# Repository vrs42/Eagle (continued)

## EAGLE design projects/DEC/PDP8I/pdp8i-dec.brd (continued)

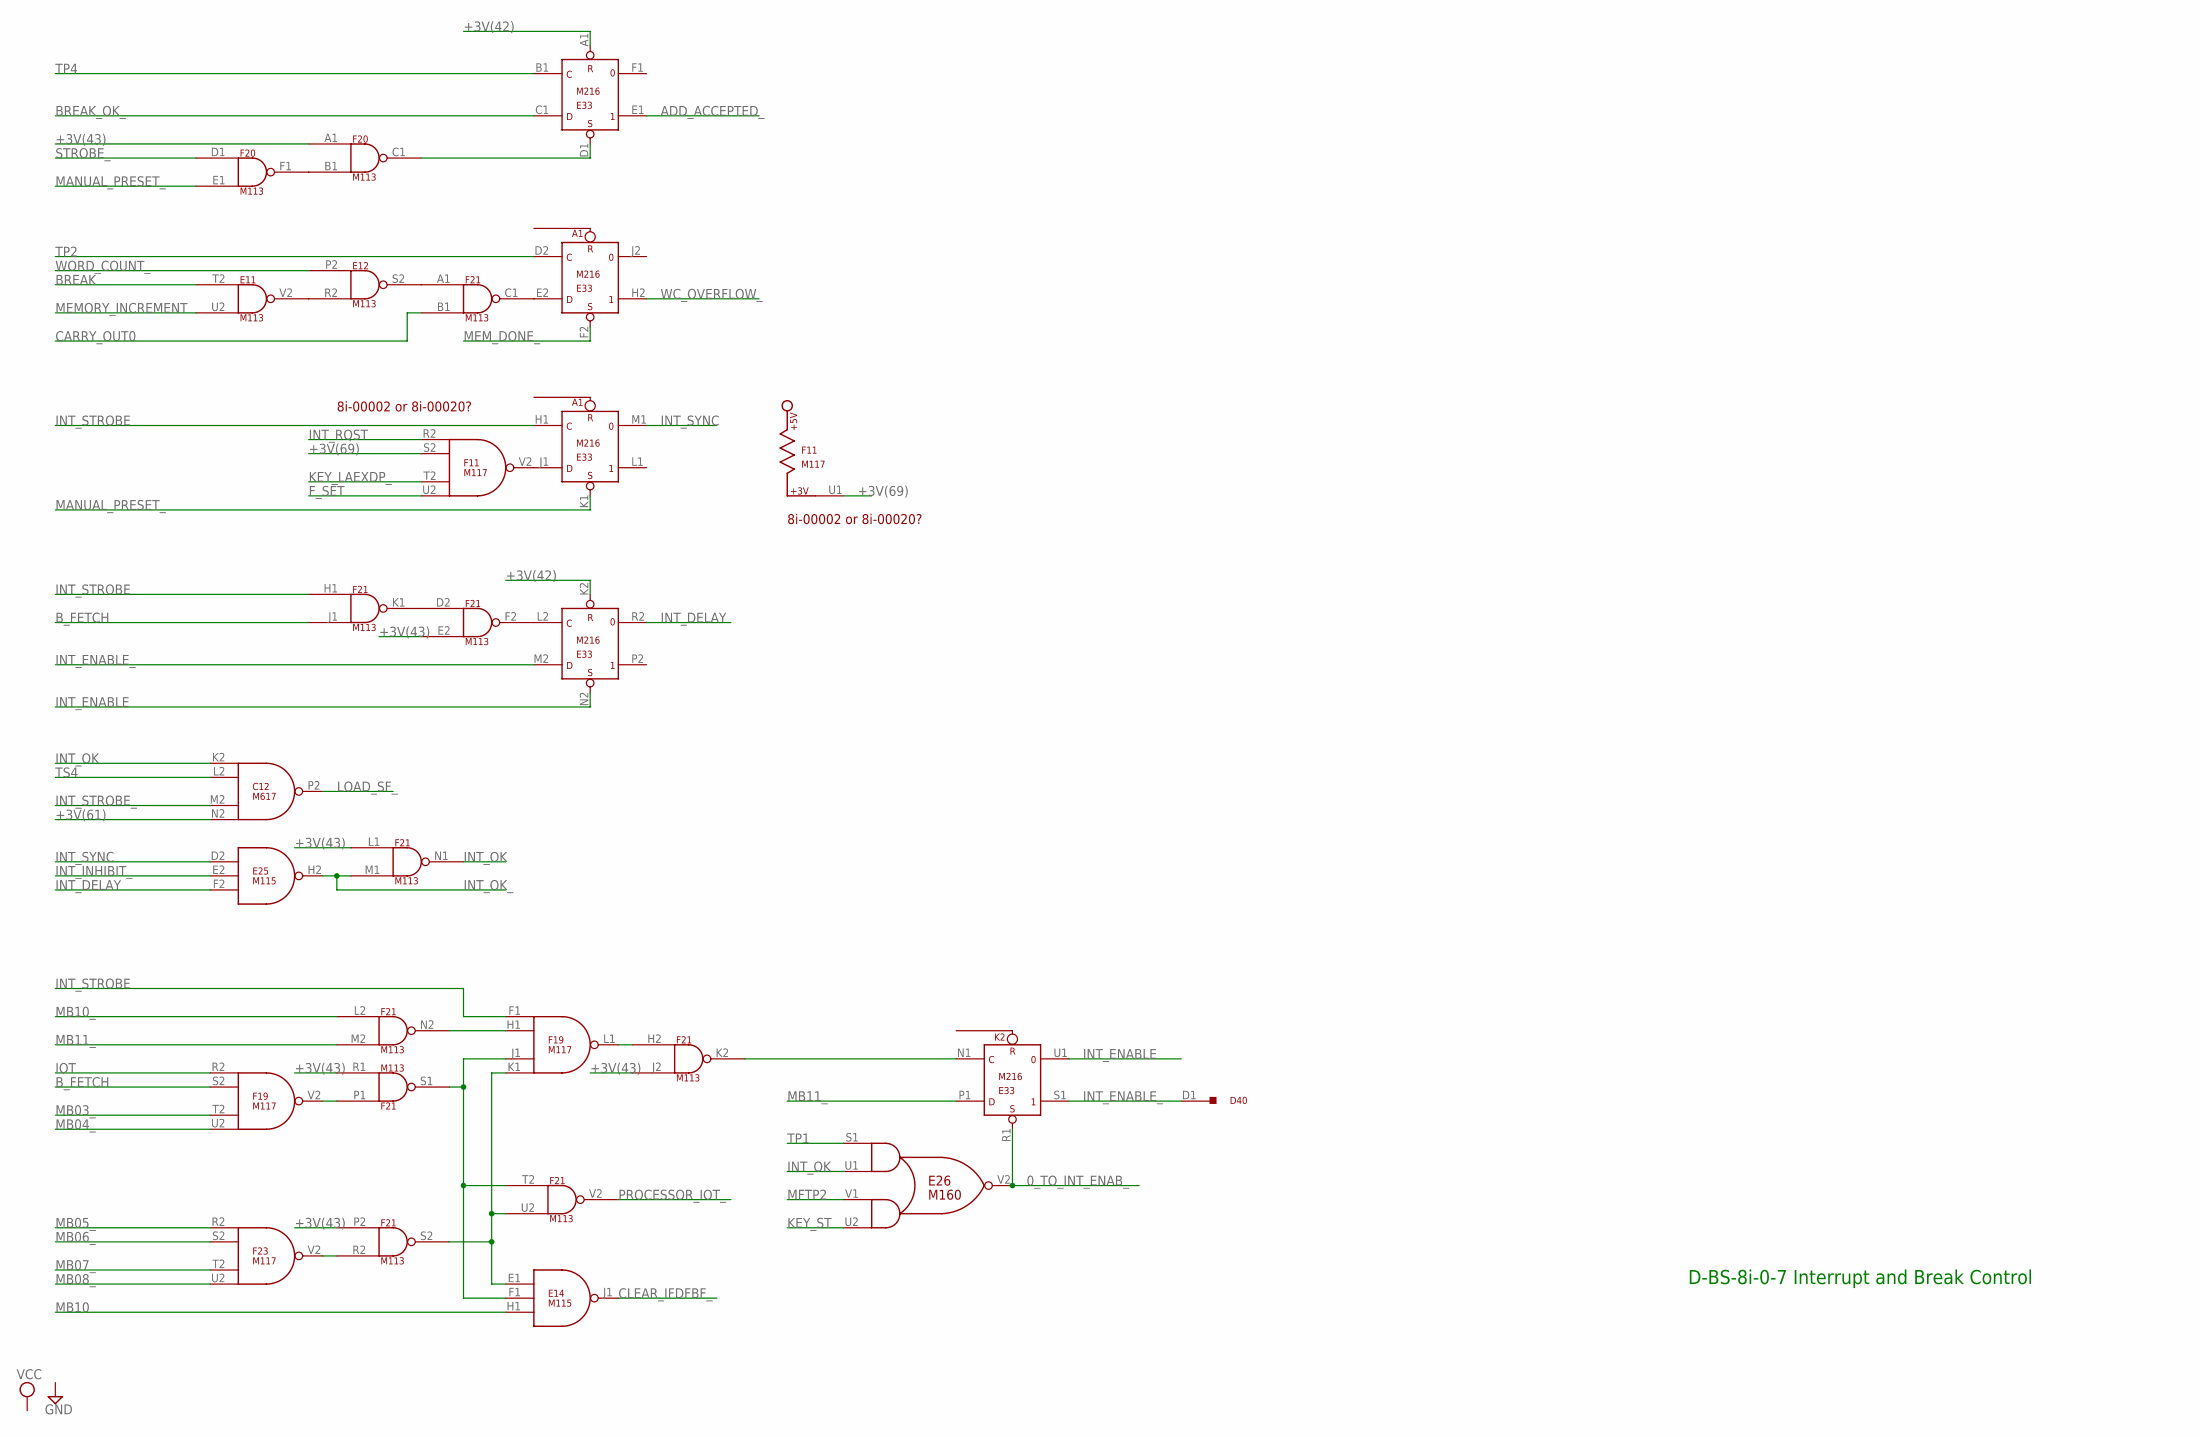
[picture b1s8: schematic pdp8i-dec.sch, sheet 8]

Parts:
C12: M617; H807
D40: M900; H807
E11, E12: M113; H807
E14, E25: M115; H807
E26: M160; H807
E33: M216; H807
F11, F19, F23: M117; H807
F20, F21: M113; H807

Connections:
0_TO_INT_ENAB_: E26.V2 (OUT), E33.R1 (S)
+3V(42): E33.A1 (R), E33.K2 (R); also elsewhere on the board
+3V(43): F20.A1 (IN1), F21.E2 (IN2), F21.J2 (IN2), F21.L1 (IN1), F21.P2 (IN1), F21.R1 (IN2); also elsewhere on the board
+3V(61): C12.N2 (IN4); also elsewhere on the board
+3V(69): F11.S2 (IN2), F11.U1; also elsewhere on the board
ADD_ACCEPTED_: E33.E1 (1); also elsewhere on the board
BREAK: E11.T2 (IN1); also elsewhere on the board
BREAK_OK_: E33.C1 (D); also elsewhere on the board
B_FETCH: F19.S2 (IN2), F21.J1 (IN2); also elsewhere on the board
CARRY_OUT0: F21.B1 (IN2); also elsewhere on the board
CLEAR_IFDFBF_: E14.J1 (OUT); also elsewhere on the board
F_SET: F11.U2 (IN4); also elsewhere on the board
GND: C12.C2 (GND), C12.T1 (GND), E11.C2 (GND), E11.T1 (GND), E12.C2 (GND), E12.T1 (GND), E14.C2 (GND), E14.T1 (GND), E25.C2 (GND), E25.T1 (GND), E26.C2 (GND), E26.T1 (GND), E33.C2 (GND), E33.T1 (GND), F11.C2 (GND), F11.T1 (GND), F19.C2 (GND), F19.T1 (GND), F20.C2 (GND), F20.T1 (GND), F21.C2 (GND), F21.T1 (GND), F23.C2 (GND), F23.T1 (GND); also elsewhere on the board
INT_DELAY: E25.F2 (IN3), E33.R2 (0)
INT_ENABLE: E33.N2 (S), E33.U1 (0)
INT_ENABLE_: D40.D1, E33.M2 (D), E33.S1 (1)
INT_INHIBIT_: E25.E2 (IN2); also elsewhere on the board
INT_OK: C12.K2 (IN1), E26.U1 (IN1B), F21.N1 (OUT); also elsewhere on the board
INT_OK_: E25.H2 (OUT), F21.M1 (IN2); also elsewhere on the board
INT_RQST: F11.R2 (IN1); also elsewhere on the board
INT_STROBE: E33.H1 (C), F19.F1 (IN1), F21.H1 (IN1); also elsewhere on the board
INT_STROBE_: C12.M2 (IN3); also elsewhere on the board
INT_SYNC: E25.D2 (IN1), E33.M1 (0)
IOT: F19.R2 (IN1); also elsewhere on the board
KEY_LAEXDP_: F11.T2 (IN3); also elsewhere on the board
KEY_ST: E26.U2 (IN2B); also elsewhere on the board
LOAD_SF_: C12.P2 (OUT); also elsewhere on the board
MANUAL_PRESET_: E33.K1 (S), F20.E1 (IN2); also elsewhere on the board
MB03_: F19.T2 (IN3); also elsewhere on the board
MB04_: F19.U2 (IN4); also elsewhere on the board
MB05_: F23.R2 (IN1); also elsewhere on the board
MB06_: F23.S2 (IN2); also elsewhere on the board
MB07_: F23.T2 (IN3); also elsewhere on the board
MB08_: F23.U2 (IN4); also elsewhere on the board
MB10: E14.H1 (IN3); also elsewhere on the board
MB10_: F21.L2 (IN1); also elsewhere on the board
MB11_: E33.P1 (D), F21.M2 (IN2); also elsewhere on the board
MEMORY_INCREMENT: E11.U2 (IN2); also elsewhere on the board
MEM_DONE_: E33.F2 (S); also elsewhere on the board
MFTP2: E26.V1 (IN2A); also elsewhere on the board
unnamed: E33.J1 (D), F11.V2 (OUT)
unnamed: F20.B1 (IN2), F20.F1 (OUT)
unnamed: E33.D1 (S), F20.C1 (OUT)
unnamed: E11.V2 (OUT), E12.R2 (IN2)
unnamed: E12.S2 (OUT), F21.A1 (IN1)
unnamed: E33.E2 (D), F21.C1 (OUT)
unnamed: F21.D2 (IN1), F21.K1 (OUT)
unnamed: E33.L2 (C), F21.F2 (OUT)
unnamed: E33.N1 (C), F21.K2 (OUT)
unnamed: F19.H1 (IN2), F21.N2 (OUT)
unnamed: E14.F1 (IN2), F19.J1 (IN3), F21.S1 (OUT), F21.T2 (IN1)
unnamed: F19.V2 (OUT), F21.P1 (IN1)
unnamed: F19.L1 (OUT), F21.H2 (IN1)
unnamed: F21.R2 (IN2), F23.V2 (OUT)
unnamed: E14.E1 (IN1), F19.K1 (IN4), F21.S2 (OUT), F21.U2 (IN2)
PROCESSOR_IOT_: F21.V2 (OUT); also elsewhere on the board
STROBE_: F20.D1 (IN1); also elsewhere on the board
TP1: E26.S1 (IN1A); also elsewhere on the board
TP2: E33.D2 (C); also elsewhere on the board
TP4: E33.B1 (C); also elsewhere on the board
TS4: C12.L2 (IN2); also elsewhere on the board
VCC: C12.A2 (VCC), E11.A2 (VCC), E12.A2 (VCC), E14.A2 (VCC), E25.A2 (VCC), E26.A2 (VCC), E33.A2 (VCC), F11.A2 (VCC), F19.A2 (VCC), F20.A2 (VCC), F21.A2 (VCC), F23.A2 (VCC); also elsewhere on the board
WC_OVERFLOW_: E33.H2 (1); also elsewhere on the board
WORD_COUNT_: E12.P2 (IN1); also elsewhere on the board

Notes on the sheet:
D-BS-8i-0-7 Interrupt and Break Control
8i-00002 or 8i-00020?

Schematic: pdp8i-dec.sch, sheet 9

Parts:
C40: M900; H807
E33: M216; H807
E40: M900; H807
EF34, EF35, EF36, EF37, EF38, EF39: M220; H807-2
F28: M115; H807
F32: M113; H807
F33: M160; H807
F40: M900; H807

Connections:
+3V(42): E33.U2 (S); also elsewhere on the board
+3V(48): F32.P2 (IN1), F32.R1 (IN2), F32.T2 (IN1), F33.C1 (IN1C), F33.D2 (IN1A), F33.P1 (IN5C); also elsewhere on the board
AC00: EF34.BA1, F33.N2 (IN4A); also elsewhere on the board
AC00_: E40.V2, EF34.BB1; also elsewhere on the board
AC01: EF34.AV1; also elsewhere on the board
AC01_: E40.T2, EF34.AV2; also elsewhere on the board
AC02: EF35.BA1; also elsewhere on the board
AC02_: E40.J1, EF35.BB1; also elsewhere on the board
AC03: EF35.AV1; also elsewhere on the board
AC03_: E40.H2, EF35.AV2; also elsewhere on the board
AC04: EF36.BA1; also elsewhere on the board
AC04_: E40.M1, EF36.BB1; also elsewhere on the board
AC05: EF36.AV1; also elsewhere on the board
AC05_: E40.B1, EF36.AV2; also elsewhere on the board
AC06: EF37.BA1; also elsewhere on the board
AC06_: EF37.BB1, F40.V2; also elsewhere on the board
AC07: EF37.AV1; also elsewhere on the board
AC07_: EF37.AV2, F40.T2; also elsewhere on the board
AC08: EF38.BA1; also elsewhere on the board
AC08_: EF38.BB1, F40.J1; also elsewhere on the board
AC09: EF38.AV1; also elsewhere on the board
AC09_: EF38.AV2, F40.H2; also elsewhere on the board
AC10: EF39.BA1; also elsewhere on the board
AC10_: EF39.BB1, F40.M1; also elsewhere on the board
AC11: EF39.AV1; also elsewhere on the board
AC11_: EF39.AV2, F40.B1; also elsewhere on the board
AC_LOAD: E33.S2 (C), EF34.AU1, EF35.AU1, EF36.AU1, EF37.AU1, EF38.AU1, EF39.AU1; also elsewhere on the board
ADDER00: F33.K1 (IN4A); also elsewhere on the board
ADDER01: F33.M1 (IN5A); also elsewhere on the board
ADDER10: F33.E1 (IN2A); also elsewhere on the board
ADDER11: F32.P1 (IN1); also elsewhere on the board
ADDER11_: F28.P1 (IN1), F32.S1 (OUT); also elsewhere on the board
ADDER_L_: F33.H1 (IN3A), F33.V2 (OUT); also elsewhere on the board
ASR_ENABLE: F33.R2 (IN4C); also elsewhere on the board
ASR_L_SET_: F33.B1 (IN1B); also elsewhere on the board
B_EAE_ON: F33.P2 (IN4B); also elsewhere on the board
CARRY_OUT0: F32.V2 (OUT), F33.U1 (IN1B); also elsewhere on the board
CARRY_OUT0_: F32.U2 (IN2), F33.U2 (IN2B); also elsewhere on the board
DOUBLE_LEFT_ROTATE: F33.N1 (IN5B); also elsewhere on the board
DOUBLE_RIGHT_ROTATE: F33.F1 (IN2B); also elsewhere on the board
EAE_IR2_: F33.S2 (IN4D); also elsewhere on the board
EAE_ON_: F28.R1 (IN2); also elsewhere on the board
GND: C40.C2, E33.C2 (GND), E33.T1 (GND), E40.C2, EF34.AC2 (GND), EF34.AT1 (GND), EF34.BC2 (GND), EF34.BT1 (GND), EF35.AC2 (GND), EF35.AT1 (GND), EF35.BC2 (GND), EF35.BT1 (GND), EF36.AC2 (GND), EF36.AT1 (GND), EF36.BC2 (GND), EF36.BT1 (GND), EF37.AC2 (GND), EF37.AT1 (GND), EF37.BC2 (GND), EF37.BT1 (GND), EF38.AC2 (GND), EF38.AT1 (GND), EF38.BC2 (GND), EF38.BT1 (GND), EF39.AC2 (GND), EF39.AT1 (GND), EF39.BC2 (GND), EF39.BT1 (GND), F28.C2 (GND), F28.T1 (GND), F32.C2 (GND), F32.T1 (GND), F33.C2 (GND), F33.T1 (GND), F40.C2; also elsewhere on the board
LBAR_ENABLE: F33.M2 (IN3B); also elsewhere on the board
LEFT_SHIFT: F33.L1 (IN4B); also elsewhere on the board
LINK: E33.V2 (1), F33.J2 (IN2A); also elsewhere on the board
LINK_: C40.B1, E33.V1 (0), F33.L2 (IN3A)
L_ENABLE: F33.K2 (IN2B); also elsewhere on the board
MA00: EF34.AM2; also elsewhere on the board
MA00_: E40.U2, EF34.AM1; also elsewhere on the board
MA01: EF34.AL2; also elsewhere on the board
MA01_: E40.R2, EF34.AL1; also elsewhere on the board
MA02: EF35.AM2; also elsewhere on the board
MA02_: E40.K2, EF35.AM1; also elsewhere on the board
MA03: EF35.AL2; also elsewhere on the board
MA03_: E40.E2, EF35.AL1; also elsewhere on the board
MA04: EF36.AM2; also elsewhere on the board
MA04_: E40.L1, EF36.AM1; also elsewhere on the board
MA05: EF36.AL2; also elsewhere on the board
MA05_: E40.E1, EF36.AL1; also elsewhere on the board
MA06: EF37.AM2; also elsewhere on the board
MA06_: EF37.AM1, F40.U2; also elsewhere on the board
MA07: EF37.AL2; also elsewhere on the board
MA07_: EF37.AL1, F40.R2; also elsewhere on the board
MA08: EF38.AM2; also elsewhere on the board
MA08_: EF38.AM1, F40.K2; also elsewhere on the board
MA09: EF38.AL2; also elsewhere on the board
MA09_: EF38.AL1, F40.E2; also elsewhere on the board
MA10: EF39.AM2; also elsewhere on the board
MA10_: EF39.AM1, F40.L1; also elsewhere on the board
MA11: EF39.AL2; also elsewhere on the board
MA11_: EF39.AL1, F40.E1; also elsewhere on the board
MA_LOAD: EF34.AK1, EF35.AK1, EF36.AK1, EF37.AK1, EF38.AK1, EF39.AK1; also elsewhere on the board
MB00: EF34.AT2; also elsewhere on the board
MB00_: E40.R1, EF34.AU2; also elsewhere on the board
MB01: EF34.AS2; also elsewhere on the board
MB01_: E40.P1, EF34.AS1; also elsewhere on the board
MB02: EF35.AT2; also elsewhere on the board
MB02_: E40.F2, EF35.AU2; also elsewhere on the board
MB03: EF35.AS2; also elsewhere on the board
MB03_: E40.D2, EF35.AS1; also elsewhere on the board
MB04: EF36.AT2; also elsewhere on the board
MB04_: E40.K1, EF36.AU2; also elsewhere on the board
MB05: EF36.AS2; also elsewhere on the board
MB05_: E40.A1, EF36.AS1; also elsewhere on the board
MB06: EF37.AT2; also elsewhere on the board
MB06_: EF37.AU2, F40.R1; also elsewhere on the board
MB07: EF37.AS2; also elsewhere on the board
MB07_: EF37.AS1, F40.P1; also elsewhere on the board
MB08: EF38.AT2; also elsewhere on the board
MB08_: EF38.AU2, F40.F2; also elsewhere on the board
MB09: EF38.AS2; also elsewhere on the board
MB09_: EF38.AS1, F40.D2; also elsewhere on the board
MB10: EF39.AT2; also elsewhere on the board
MB10_: EF39.AU2, F40.K1; also elsewhere on the board
MB11: EF39.AS2; also elsewhere on the board
MB11_: EF39.AS1, F40.A1; also elsewhere on the board
MB_LOAD: EF34.AR1, EF35.AR1, EF36.AR1, EF37.AR1, EF38.AR1, EF39.AR1; also elsewhere on the board
unnamed: E33.T2 (D), F33.R1 (OUT)
unnamed: F32.S2 (OUT), F33.V1 (IN2A)
unnamed: F28.U1 (OUT), F33.A1 (IN1A)
unnamed: F32.R2 (IN2), F33.S1 (IN1A), F33.T2 (OUT)
NO_SHIFT: F33.J1 (IN3B); also elsewhere on the board
PC00_: E40.J2, EF34.AR2
PC01_: E40.S1, EF34.AP2
PC02_: E40.P2, EF35.AR2
PC03_: E40.N1, EF35.AP2
PC04_: E40.C1, EF36.AR2
PC05_: E40.D1, EF36.AP2
PC06_: EF37.AR2, F40.J2
PC07_: EF37.AP2, F40.S1
PC08_: EF38.AR2, F40.P2
PC09_: EF38.AP2, F40.N1
PC10_: EF39.AR2, F40.C1
PC11_: EF39.AP2, F40.D1
PC_LOAD: EF34.AN2, EF35.AN2, EF36.AN2, EF37.AN2, EF38.AN2, EF39.AN2; also elsewhere on the board
RIGHT_SHIFT: F33.D1 (IN1D); also elsewhere on the board
TT_DATA: F33.H2 (IN1D); also elsewhere on the board
TT_INST_: F28.S1 (IN3), F33.F2 (IN1C); also elsewhere on the board
TT_SHIFT_ENABLE: F33.E2 (IN1B); also elsewhere on the board
VCC: C40.A2, E33.A2 (VCC), E40.A2, EF34.AA2 (VCC), EF34.BA2 (VCC), EF35.AA2 (VCC), EF35.BA2 (VCC), EF36.AA2 (VCC), EF36.BA2 (VCC), EF37.AA2 (VCC), EF37.BA2 (VCC), EF38.AA2 (VCC), EF38.BA2 (VCC), EF39.AA2 (VCC), EF39.BA2 (VCC), F28.A2 (VCC), F32.A2 (VCC), F33.A2 (VCC), F40.A2; also elsewhere on the board

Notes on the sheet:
D-BS-8i-0-8 Major Registers
REG_BUS00
REG_BUS01
REG_BUS02
REG_BUS03
REG_BUS04
REG_BUS05
REG_BUS06
REG_BUS07
REG_BUS08
REG_BUS09
REG_BUS10
REG_BUS11

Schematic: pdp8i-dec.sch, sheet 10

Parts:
A40: W077; H807
EF34, EF35: M220; H807-2

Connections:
ACBAR_ENABLE: EF34.BJ2, EF35.BJ2; also elsewhere on the board
AC_ENABLE: EF34.BH2, EF35.BH2; also elsewhere on the board
ADDER00: EF34.AE2, EF35.AB1; also elsewhere on the board
ADDER01: EF34.AF1, EF35.AC1; also elsewhere on the board
ADDER02: EF34.AH2, EF35.AE2, EF35.BB2; also elsewhere on the board
ADDER03: EF34.AJ2, EF35.AF1; also elsewhere on the board
ADDER04: EF35.AH2; also elsewhere on the board
ADDER05: EF35.AJ2; also elsewhere on the board
ADDER11: EF34.AB1; also elsewhere on the board
ADDER_L_: EF34.AC1, EF34.BB2; also elsewhere on the board
AND_ENABLE: EF34.AA1, EF35.AA1; also elsewhere on the board
CARRY_OUT0_: EF34.BK2; also elsewhere on the board
DATA00: EF34.BM2; also elsewhere on the board
DATA01: EF34.BP2; also elsewhere on the board
DATA02: EF35.BM2; also elsewhere on the board
DATA_ADD00: EF34.BS1; also elsewhere on the board
DATA_ADD01: EF34.BU1; also elsewhere on the board
DATA_ADD02: EF35.BS1; also elsewhere on the board
DATA_ADD_ENABLE: EF34.BT2, EF35.BT2; also elsewhere on the board
DATA_ENABLE: EF34.BL1, EF35.BL1; also elsewhere on the board
DOUBLE_LEFT_ROTATE: EF34.AH1, EF35.AH1; also elsewhere on the board
DOUBLE_RIGHT_ROTATE: EF34.AD1, EF35.AD1; also elsewhere on the board
GND: EF34.AC2 (GND), EF34.AT1 (GND), EF34.BC2 (GND), EF34.BD1, EF34.BE2, EF34.BN1, EF34.BT1 (GND), EF35.AC2 (GND), EF35.AT1 (GND), EF35.BC2 (GND), EF35.BD1, EF35.BT1 (GND); also elsewhere on the board
INPUT_BUS00: EF34.BK1; also elsewhere on the board
INPUT_BUS01: EF34.BM1; also elsewhere on the board
INPUT_BUS02: EF35.BK1; also elsewhere on the board
IO_ENABLE: EF34.BL2, EF35.BL2; also elsewhere on the board
LEFT_SHIFT: EF34.AF2, EF35.AF2; also elsewhere on the board
MA_ENABLE0_4: EF34.BP1, EF34.BR2, EF35.BP1; also elsewhere on the board
MEM00: EF34.BR1; also elsewhere on the board
MEM01: EF34.BV2; also elsewhere on the board
MEM02: EF35.BR1; also elsewhere on the board
MEM_ENABLE0_4: EF34.BU2, EF34.BV1, EF35.BU2; also elsewhere on the board
MQ00: EF34.BH1; also elsewhere on the board
MQ01: EF34.BN2; also elsewhere on the board
MQ02: EF35.BH1; also elsewhere on the board
MQ_ENABLE: EF34.BF1, EF35.BF1; also elsewhere on the board
unnamed: EF34.BJ1, EF35.BK2
NO_SHIFT: EF34.AE1, EF35.AE1; also elsewhere on the board
PC_ENABLE: EF34.BS2, EF35.BS2; also elsewhere on the board
RIGHT_SHIFT: EF34.AD2, EF35.AD2; also elsewhere on the board
SC_ENABLE: EF34.BF2, EF35.BF2; also elsewhere on the board
SR00: A40.L2, EF34.BE1
SR01: A40.M2, EF34.BD2
SR02: A40.R2, EF35.BE1
SR_ENABLE: EF34.BC1, EF35.BC1; also elsewhere on the board
TT_LINE_SHIFT_: EF34.AB2, EF35.AB2; also elsewhere on the board
VCC: EF34.AA2 (VCC), EF34.BA2 (VCC), EF35.AA2 (VCC), EF35.BA2 (VCC); also elsewhere on the board

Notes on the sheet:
D-BS-8i-0-9 Major Registers Gating (1/4)
REG_BUS00
REG_BUS01
REG_BUS02
CARRY_OUT3_

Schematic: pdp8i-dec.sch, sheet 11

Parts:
A40: W077; H807
EF35, EF36: M220; H807-2

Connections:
ACBAR_ENABLE: EF36.BJ2; also elsewhere on the board
AC_ENABLE: EF36.BH2; also elsewhere on the board
ADDER02: EF36.AB1; also elsewhere on the board
ADDER03: EF36.AC1; also elsewhere on the board
ADDER04: EF36.AE2, EF36.BB2; also elsewhere on the board
ADDER05: EF36.AF1; also elsewhere on the board
ADDER06: EF36.AH2; also elsewhere on the board
ADDER07: EF36.AJ2; also elsewhere on the board
AND_ENABLE: EF36.AA1; also elsewhere on the board
CARRY_OUT6_: EF36.BJ1; also elsewhere on the board
DATA03: EF35.BP2; also elsewhere on the board
DATA04: EF36.BM2; also elsewhere on the board
DATA05: EF36.BP2; also elsewhere on the board
DATA_ADD03: EF35.BU1; also elsewhere on the board
DATA_ADD04: EF36.BS1; also elsewhere on the board
DATA_ADD05: EF36.BU1; also elsewhere on the board
DATA_ADD_ENABLE: EF36.BT2; also elsewhere on the board
DATA_ENABLE: EF36.BL1; also elsewhere on the board
DOUBLE_LEFT_ROTATE: EF36.AH1; also elsewhere on the board
DOUBLE_RIGHT_ROTATE: EF36.AD1; also elsewhere on the board
GND: EF35.AC2 (GND), EF35.AT1 (GND), EF35.BC2 (GND), EF35.BE2, EF35.BN1, EF35.BT1 (GND), EF36.AC2 (GND), EF36.AT1 (GND), EF36.BC2 (GND), EF36.BD1, EF36.BE2, EF36.BN1, EF36.BT1 (GND); also elsewhere on the board
INPUT_BUS03: EF35.BM1; also elsewhere on the board
INPUT_BUS04: EF36.BK1; also elsewhere on the board
INPUT_BUS05: EF36.BM1; also elsewhere on the board
IO_ENABLE: EF36.BL2; also elsewhere on the board
LEFT_SHIFT: EF36.AF2; also elsewhere on the board
MA_ENABLE0_4: EF35.BR2, EF36.BP1; also elsewhere on the board
MA_ENABLE5_11: EF36.BR2; also elsewhere on the board
MEM03: EF35.BV2; also elsewhere on the board
MEM04: EF36.BR1; also elsewhere on the board
MEM05: EF36.BV2; also elsewhere on the board
MEM_ENABLE0_4: EF35.BV1, EF36.BU2; also elsewhere on the board
MEM_ENABLE5_8: EF36.BV1; also elsewhere on the board
MQ03: EF35.BN2; also elsewhere on the board
MQ04: EF36.BH1; also elsewhere on the board
MQ05: EF36.BN2; also elsewhere on the board
MQ_ENABLE: EF36.BF1; also elsewhere on the board
unnamed: EF35.BJ1, EF36.BK2
NO_SHIFT: EF36.AE1; also elsewhere on the board
PC_ENABLE: EF36.BS2; also elsewhere on the board
RIGHT_SHIFT: EF36.AD2; also elsewhere on the board
SC_ENABLE: EF36.BF2; also elsewhere on the board
SR03: A40.S2, EF35.BD2
SR04: A40.T2, EF36.BE1
SR05: A40.U2, EF36.BD2
SR_ENABLE: EF36.BC1; also elsewhere on the board
TT_LINE_SHIFT_: EF36.AB2; also elsewhere on the board
VCC: EF35.AA2 (VCC), EF35.BA2 (VCC), EF36.AA2 (VCC), EF36.BA2 (VCC); also elsewhere on the board

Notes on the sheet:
D-BS-8i-0-9 Major Registers Gating (2/4)
REG_BUS03
REG_BUS04
REG_BUS05

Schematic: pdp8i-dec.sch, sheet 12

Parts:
A40: W077; H807
B40: W077; H807
EF37, EF38: M220; H807-2

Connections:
ACBAR_ENABLE: EF37.BJ2, EF38.BJ2; also elsewhere on the board
AC_ENABLE: EF37.BH2, EF38.BH2; also elsewhere on the board
ADDER04: EF37.AB1; also elsewhere on the board
ADDER05: EF37.AC1; also elsewhere on the board
ADDER06: EF37.AE2, EF37.BB2, EF38.AB1; also elsewhere on the board
ADDER07: EF37.AF1, EF38.AC1; also elsewhere on the board
ADDER08: EF37.AH2, EF38.AE2, EF38.BB2; also elsewhere on the board
ADDER09: EF37.AJ2, EF38.AF1; also elsewhere on the board
ADDER10: EF38.AH2; also elsewhere on the board
ADDER11: EF38.AJ2; also elsewhere on the board
AND_ENABLE: EF37.AA1, EF38.AA1; also elsewhere on the board
CARRY_OUT6_: EF37.BK2; also elsewhere on the board
DATA06: EF37.BM2; also elsewhere on the board
DATA07: EF37.BP2; also elsewhere on the board
DATA08: EF38.BM2; also elsewhere on the board
DATA_ADD06: EF37.BS1; also elsewhere on the board
DATA_ADD07: EF37.BU1; also elsewhere on the board
DATA_ADD08: EF38.BS1; also elsewhere on the board
DATA_ADD_ENABLE: EF37.BT2, EF38.BT2; also elsewhere on the board
DATA_ENABLE: EF37.BL1, EF38.BL1; also elsewhere on the board
DOUBLE_LEFT_ROTATE: EF37.AH1, EF38.AH1; also elsewhere on the board
DOUBLE_RIGHT_ROTATE: EF37.AD1, EF38.AD1; also elsewhere on the board
GND: A40.C2, B40.C2, EF37.AC2 (GND), EF37.AT1 (GND), EF37.BC2 (GND), EF37.BD1, EF37.BE2, EF37.BT1 (GND), EF38.AC2 (GND), EF38.AT1 (GND), EF38.BC2 (GND), EF38.BT1 (GND); also elsewhere on the board
INPUT_BUS06: EF37.BK1; also elsewhere on the board
INPUT_BUS07: EF37.BM1; also elsewhere on the board
INPUT_BUS08: EF38.BK1; also elsewhere on the board
IO_ENABLE: EF37.BL2, EF38.BL2; also elsewhere on the board
LEFT_SHIFT: EF37.AF2, EF38.AF2; also elsewhere on the board
MA_ENABLE5_11: EF37.BP1, EF37.BR2, EF38.BP1; also elsewhere on the board
MEM06: EF37.BR1; also elsewhere on the board
MEM07: EF37.BV2; also elsewhere on the board
MEM08: EF38.BR1; also elsewhere on the board
MEM_ENABLE5_8: EF37.BU2, EF37.BV1, EF38.BU2; also elsewhere on the board
MQ06: EF37.BH1; also elsewhere on the board
MQ07: EF37.BN2; also elsewhere on the board
MQ08: EF38.BH1; also elsewhere on the board
MQ_ENABLE: EF37.BF1, EF38.BF1; also elsewhere on the board
unnamed: EF37.BJ1, EF38.BK2
NO_SHIFT: EF37.AE1, EF38.AE1; also elsewhere on the board
PC_ENABLE: EF37.BS2, EF38.BS2; also elsewhere on the board
RIGHT_SHIFT: EF37.AD2, EF38.AD2; also elsewhere on the board
SC0: EF37.BN1; also elsewhere on the board
SC1: EF38.BD1; also elsewhere on the board
SC_ENABLE: EF37.BF2, EF38.BF2; also elsewhere on the board
SR06: A40.V2, EF37.BE1
SR07: B40.D2, EF37.BD2
SR08: B40.E2, EF38.BE1
SR_ENABLE: EF37.BC1, EF38.BC1; also elsewhere on the board
TT_LINE_SHIFT_: EF37.AB2, EF38.AB2; also elsewhere on the board
VCC: A40.A2, B40.A2, EF37.AA2 (VCC), EF37.BA2 (VCC), EF38.AA2 (VCC), EF38.BA2 (VCC); also elsewhere on the board

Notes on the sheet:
D-BS-8i-0-9 Major Registers Gating (3/4)
REG_BUS06
REG_BUS07
REG_BUS08
CARRY_OUT9_

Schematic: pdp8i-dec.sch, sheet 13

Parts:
B40: W077; H807
E24: M113; H807
E25: M115; H807
EF38, EF39: M220; H807-2

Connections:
ACBAR_ENABLE: EF39.BJ2; also elsewhere on the board
AC_ENABLE: EF39.BH2; also elsewhere on the board
ADDER00: EF39.AJ2; also elsewhere on the board
ADDER08: EF39.AB1; also elsewhere on the board
ADDER09: EF39.AC1; also elsewhere on the board
ADDER10: EF39.AE2, EF39.BB2; also elsewhere on the board
ADDER11: EF39.AF1; also elsewhere on the board
ADDER_L_: E24.B1 (IN2); also elsewhere on the board
AND_ENABLE: EF39.AA1; also elsewhere on the board
CARRY_INSERT_: EF39.BJ1; also elsewhere on the board
DATA09: EF38.BP2; also elsewhere on the board
DATA10: EF39.BM2; also elsewhere on the board
DATA11: EF39.BP2; also elsewhere on the board
DATA_ADD09: EF38.BU1; also elsewhere on the board
DATA_ADD10: EF39.BS1; also elsewhere on the board
DATA_ADD11: EF39.BU1; also elsewhere on the board
DATA_ADD_ENABLE: EF39.BT2; also elsewhere on the board
DATA_ENABLE: EF39.BL1; also elsewhere on the board
DOUBLE_LEFT_ROTATE: EF39.AH1; also elsewhere on the board
DOUBLE_RIGHT_ROTATE: EF39.AD1; also elsewhere on the board
E25D1: E25.D1 (OUT), EF39.AH2
EAE_MQ0BAR_ENABLE_: E25.B1 (IN2); also elsewhere on the board
EAE_MQ0_ENABLE_: E25.C1 (IN3); also elsewhere on the board
EAE_ON_: E24.A1 (IN1); also elsewhere on the board
GND: E24.C2 (GND), E24.T1 (GND), E25.C2 (GND), E25.T1 (GND), EF38.AC2 (GND), EF38.AT1 (GND), EF38.BC2 (GND), EF38.BE2, EF38.BT1 (GND), EF39.AC2 (GND), EF39.AT1 (GND), EF39.BC2 (GND), EF39.BT1 (GND); also elsewhere on the board
INPUT_BUS09: EF38.BM1; also elsewhere on the board
INPUT_BUS10: EF39.BK1; also elsewhere on the board
INPUT_BUS11: EF39.BM1; also elsewhere on the board
IO_ENABLE: EF39.BL2; also elsewhere on the board
LEFT_SHIFT: EF39.AF2; also elsewhere on the board
MA_ENABLE5_11: EF38.BR2, EF39.BP1, EF39.BR2; also elsewhere on the board
MEM09: EF38.BV2; also elsewhere on the board
MEM10: EF39.BR1; also elsewhere on the board
MEM11: EF39.BV2; also elsewhere on the board
MEM_ENABLE9_11: EF38.BV1, EF39.BU2, EF39.BV1; also elsewhere on the board
MQ09: EF38.BN2; also elsewhere on the board
MQ10: EF39.BH1; also elsewhere on the board
MQ11: EF39.BN2; also elsewhere on the board
MQ_ENABLE: EF39.BF1; also elsewhere on the board
unnamed: EF38.BJ1, EF39.BK2
unnamed: E24.C1 (OUT), E25.A1 (IN1)
NO_SHIFT: EF39.AE1; also elsewhere on the board
PC_ENABLE: EF39.BS2; also elsewhere on the board
RIGHT_SHIFT: EF39.AD2; also elsewhere on the board
SC2: EF38.BN1; also elsewhere on the board
SC3: EF39.BD1; also elsewhere on the board
SC4: EF39.BN1; also elsewhere on the board
SC_ENABLE: EF39.BF2; also elsewhere on the board
SR09: B40.F2, EF38.BD2
SR10: B40.H2, EF39.BE1
SR11: B40.J2, EF39.BD2
SR_ENABLE: EF39.BC1; also elsewhere on the board
TT_CARRY_INSERT_S: EF39.BE2; also elsewhere on the board
TT_LINE_SHIFT_: EF39.AB2; also elsewhere on the board
VCC: E24.A2 (VCC), E25.A2 (VCC), EF38.AA2 (VCC), EF38.BA2 (VCC), EF39.AA2 (VCC), EF39.BA2 (VCC); also elsewhere on the board

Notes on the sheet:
D-BS-8i-0-9 Major Registers Gating (4/4)
REG_BUS09
REG_BUS10
REG_BUS11
